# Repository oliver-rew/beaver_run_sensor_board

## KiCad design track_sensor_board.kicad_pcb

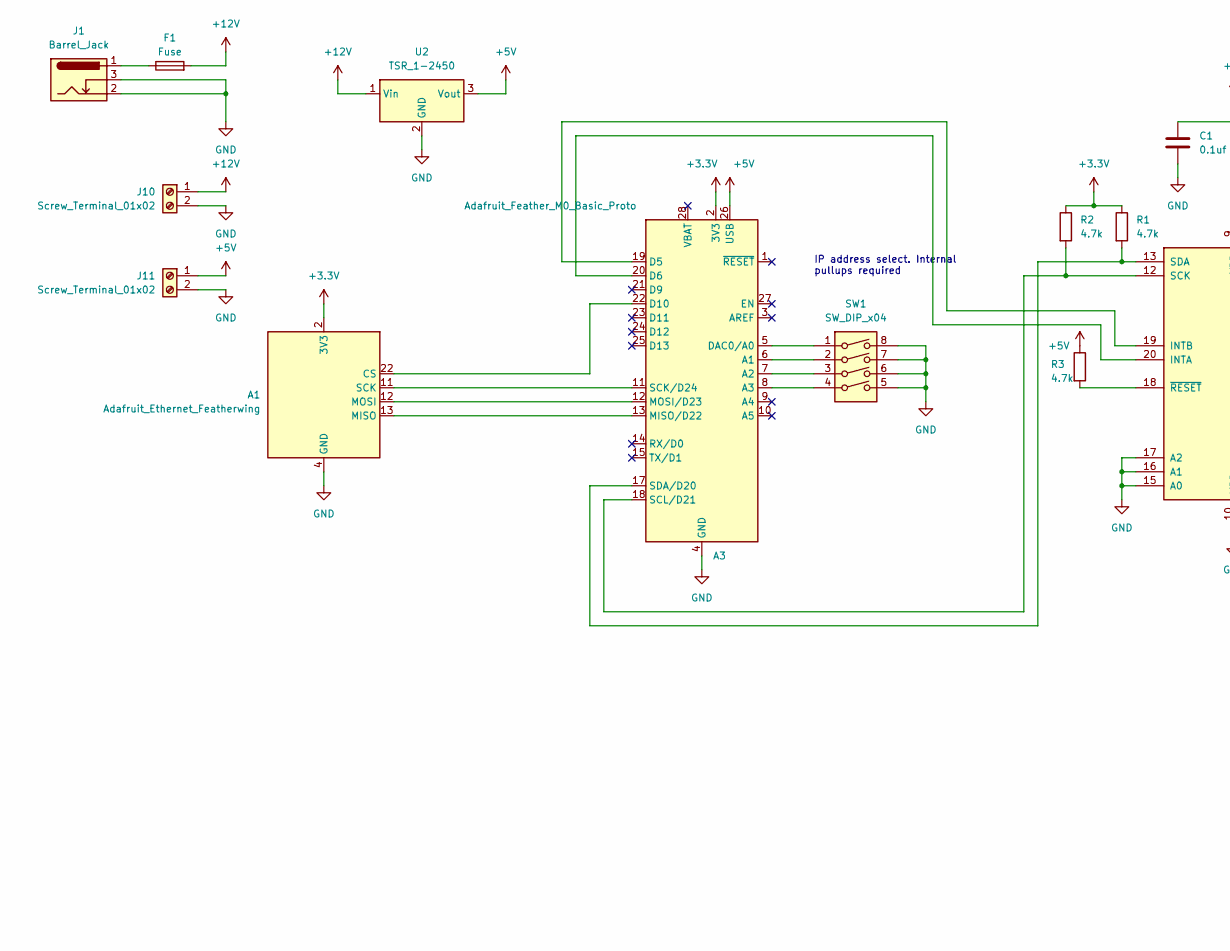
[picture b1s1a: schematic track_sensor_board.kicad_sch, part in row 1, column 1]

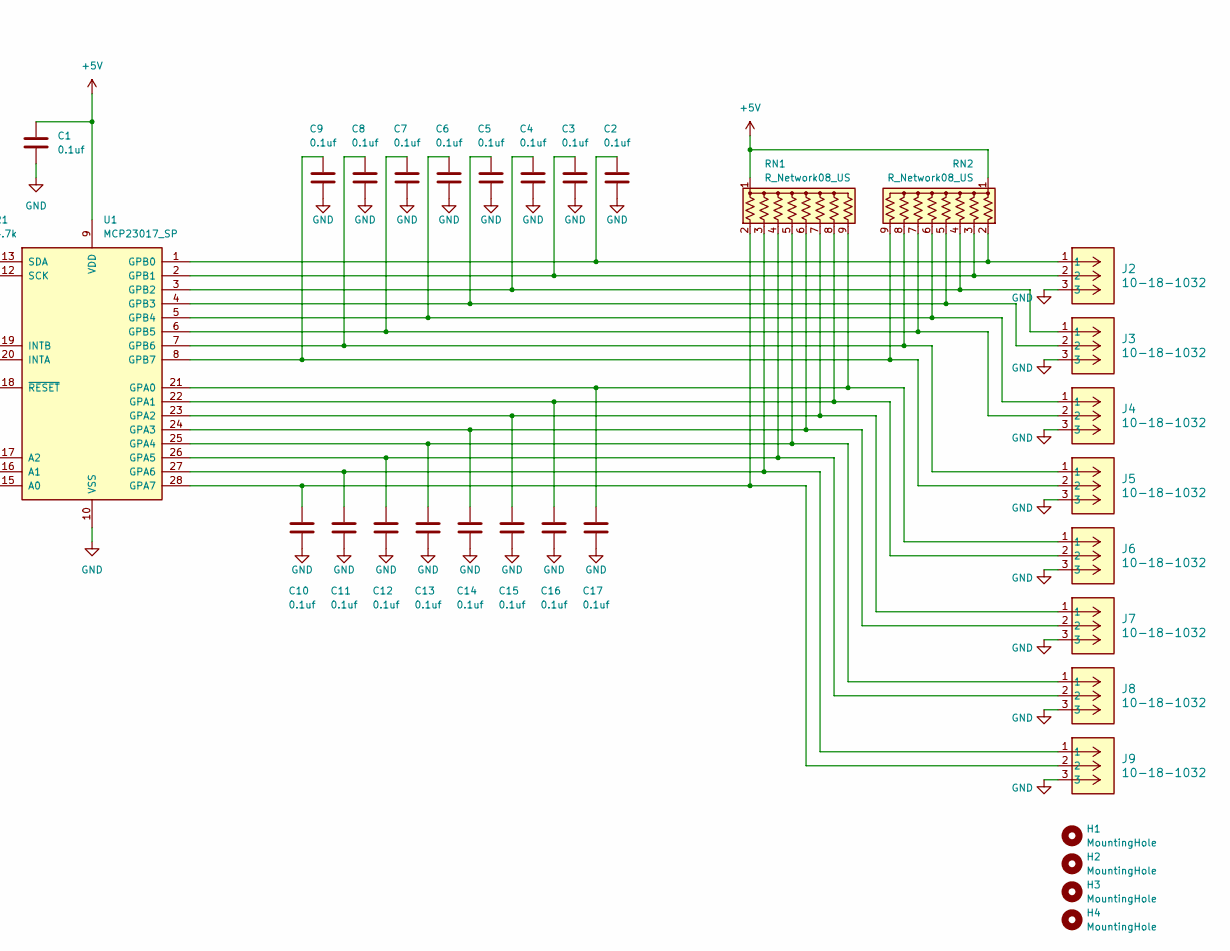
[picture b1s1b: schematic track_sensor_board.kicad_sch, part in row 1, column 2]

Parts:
A1: Adafruit_Ethernet_Featherwing
A3: Adafruit_Feather_M0_Basic_Proto; Adafruit_Feather
C1, C2, C3, C4, C5, C6, C7, C8, C9, C10, C11, C12, C13, C14, C15, C16, C17: 0.1uf; C_Disc_D3.0mm_W1.6mm_P2.50mm
F1: Fuse; Fuseholder_Blade_Mini_Keystone_3568
H1, H2, H3, H4: MountingHole; MountingHole_4.5mm
J1: Barrel_Jack; BarrelJack_Wuerth_6941xx301002
J2, J3, J4, J5, J6, J7, J8, J9: 10-18-1032; CONN_10-18-1032_MOL
J10, J11: Screw_Terminal_01x02; TerminalBlock_Phoenix_MKDS-1,5-2-5.08_1x02_P5.08mm_Horizont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
R1, R2, R3: 4.7k; R_Axial_DIN0207_L6.3mm_D2.5mm_P7.62mm_Horizontal
RN1, RN2: R_Network08_US; R_Array_SIP9
SW1: SW_DIP_x04; SW_DIP_SPSTx04_Slide_9.78x12.34mm_W7.62mm_P2.54mm
U1: MCP23017_SP; DIP-28_W7.62mm
U2: TSR_1-2450; Converter_DCDC_TRACO_TSR-1_THT

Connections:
+3.3V: A1.2 (3V3), A3.2 (3V3), R1.1, R2.1
+5V: A3.26 (USB), C1.1, J11.1, R3.1, RN1.1 (common), RN2.1 (common), U1.9 (VDD), U2.3 (Vout)
+12V: F1.2, J10.1, U2.1 (Vin)
GND: A1.4 (GND), A3.4 (GND), A3.16 (GND), C1.2, C2.2, C3.2, C4.2, C5.2, C6.2, C7.2, C8.2, C9.2, C10.2, C11.2, C12.2, C13.2, C14.2, C15.2, C16.2, C17.2, J1.2, J1.3, J2.3, J3.3, J4.3, J5.3, J6.3, J7.3, J8.3, J9.3, J10.2, J11.2, SW1.5, SW1.6, SW1.7, SW1.8, U1.10 (VSS), U1.15 (A0), U1.16 (A1), U1.17 (A2), U2.2 (GND)
unnamed: A1.22 (CS), A3.22 (D10)
unnamed: A1.13 (MISO), A3.13 (MISO/D22)
unnamed: A1.12 (MOSI), A3.12 (MOSI/D23)
unnamed: A1.11 (SCK), A3.11 (SCK/D24)
unnamed: A3.6 (A1), SW1.2
unnamed: A3.7 (A2), SW1.3
unnamed: A3.8 (A3), SW1.4
unnamed: A3.19 (D5), U1.19 (INTB)
unnamed: A3.20 (D6), U1.20 (INTA)
unnamed: A3.5 (DAC0/A0), SW1.1
unnamed: A3.18 (SCL/D21), R2.2, U1.12 (SCK)
unnamed: A3.17 (SDA/D20), R1.2, U1.13 (SDA)
unnamed: F1.1, J1.1
unnamed: C10.1, J9.2, RN1.2 (R1), U1.28 (GPA7)
unnamed: C11.1, J9.1, RN1.3 (R2), U1.27 (GPA6)
unnamed: C12.1, J8.2, RN1.4 (R3), U1.26 (GPA5)
unnamed: C13.1, J8.1, RN1.5 (R4), U1.25 (GPA4)
unnamed: C14.1, J7.2, RN1.6 (R5), U1.24 (GPA3)
unnamed: C15.1, J7.1, RN1.7 (R6), U1.23 (GPA2)
unnamed: C16.1, J6.2, RN1.8 (R7), U1.22 (GPA1)
unnamed: C17.1, J6.1, RN1.9 (R8), U1.21 (GPA0)
unnamed: C2.1, J2.1, RN2.2 (R1), U1.1 (GPB0)
unnamed: C3.1, J2.2, RN2.3 (R2), U1.2 (GPB1)
unnamed: C4.1, J3.1, RN2.4 (R3), U1.3 (GPB2)
unnamed: C5.1, J3.2, RN2.5 (R4), U1.4 (GPB3)
unnamed: C6.1, J4.1, RN2.6 (R5), U1.5 (GPB4)
unnamed: C7.1, J4.2, RN2.7 (R6), U1.6 (GPB5)
unnamed: C8.1, J5.1, RN2.8 (R7), U1.7 (GPB6)
unnamed: C9.1, J5.2, RN2.9 (R8), U1.8 (GPB7)
unnamed: R3.2, U1.18 (~RESET)

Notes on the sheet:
IP address select. Internal pullups required

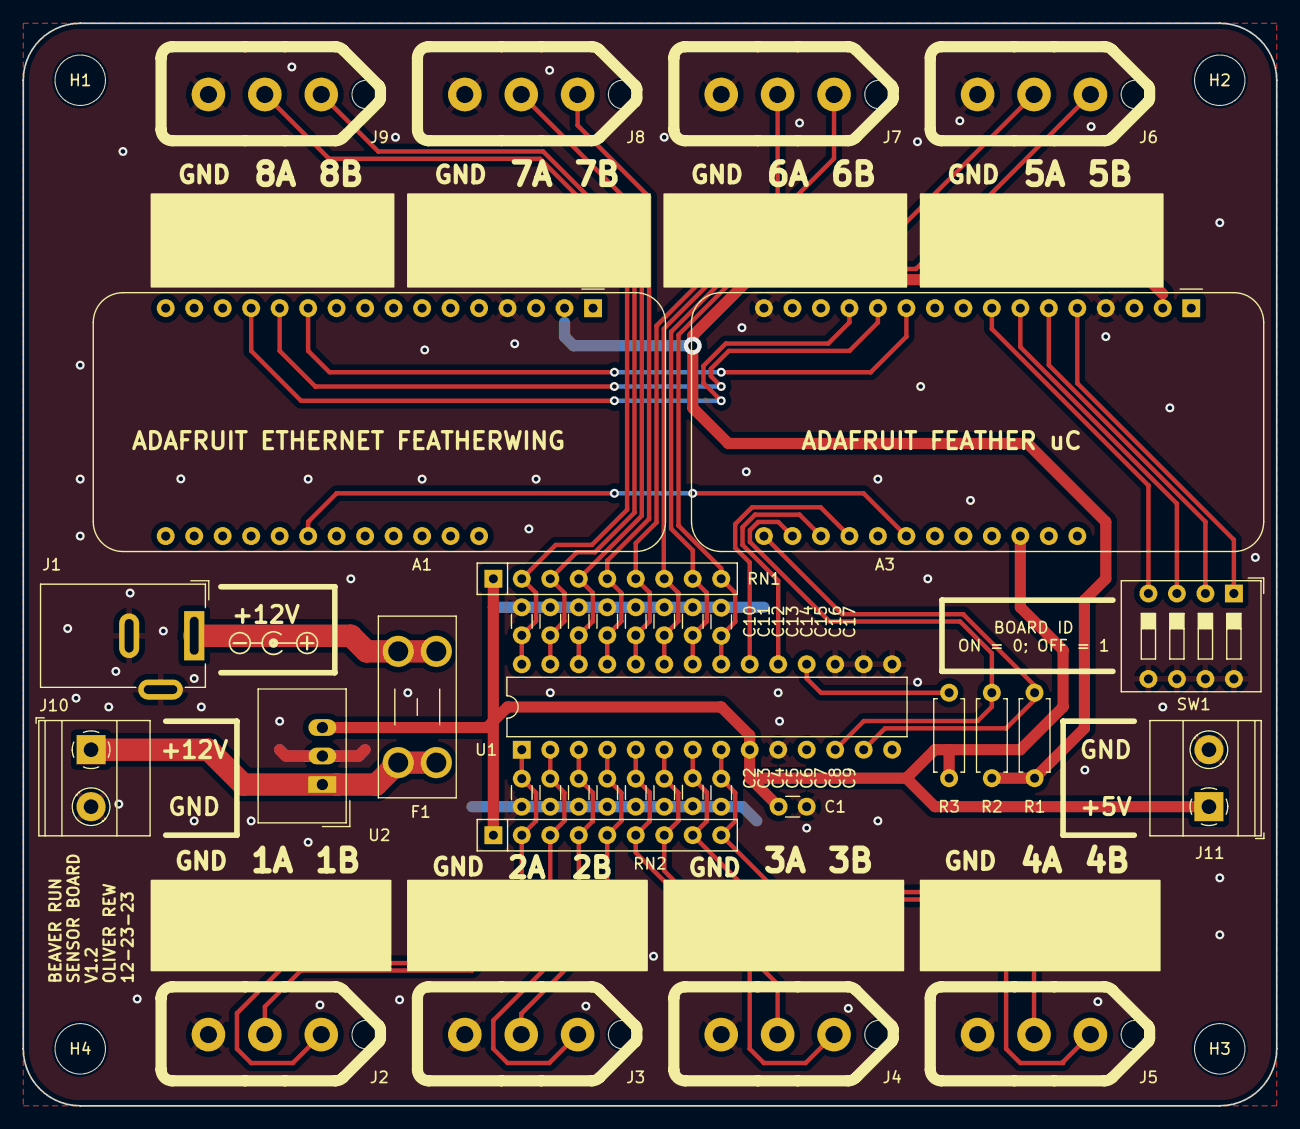
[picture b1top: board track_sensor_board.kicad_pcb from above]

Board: 2 copper layers, 111.8 x 96.5 mm, 43 parts (0 on the bottom side), 34 nets.

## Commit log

2023-11-05 feat: add board files
2023-12-17 feat: upload gerbers
2023-12-22 chore: backup before recovery
2023-12-22 chore: save after recovery, looks good
2023-12-24 feat: mostly updated v1.1
2023-12-24 feat: cleaned up a bit
2023-12-24 feat: new gerbers
2023-12-25 feat: added filter caps
2023-12-25 fix: fix grounds on caps
2023-12-25 feat: one last fix before gerbers
2023-12-25 feat: add gerbers
